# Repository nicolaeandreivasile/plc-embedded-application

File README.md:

# plc-embedded-application
A PLC (Programmable Logic Controller) made from scratch focused on controlling and maintaining industrial-like applications

## Board design
Control unit schematic under development. I/O unit schematic development process not started yet

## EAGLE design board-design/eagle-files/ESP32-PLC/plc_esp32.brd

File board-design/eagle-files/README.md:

Connected with ESP32:

	EEPROM: M95M01
	EERAM: 48L512T
	-------------- 7 pins (VSPI)
	
	RTC: MCP7940N
	-------------- 3 pins (I2C)
	
	Volt. supervisor: BD48E30G
	-------------- 1 pin (ESP enable)
	
	I/O controller
	-------------- 7 pins (HSPI)
	
	UART0
	-------------- 2 pins (RXD/TXD)
	
Unconnected with ESP32:

	LTE: EC20
	-------------- 5 pins
	
	RS-422/485: MAX3485CSA
	-------------- 4 pins
	
	+ other optional modules
	
No pins left for ESP32 module! Another approach needed.

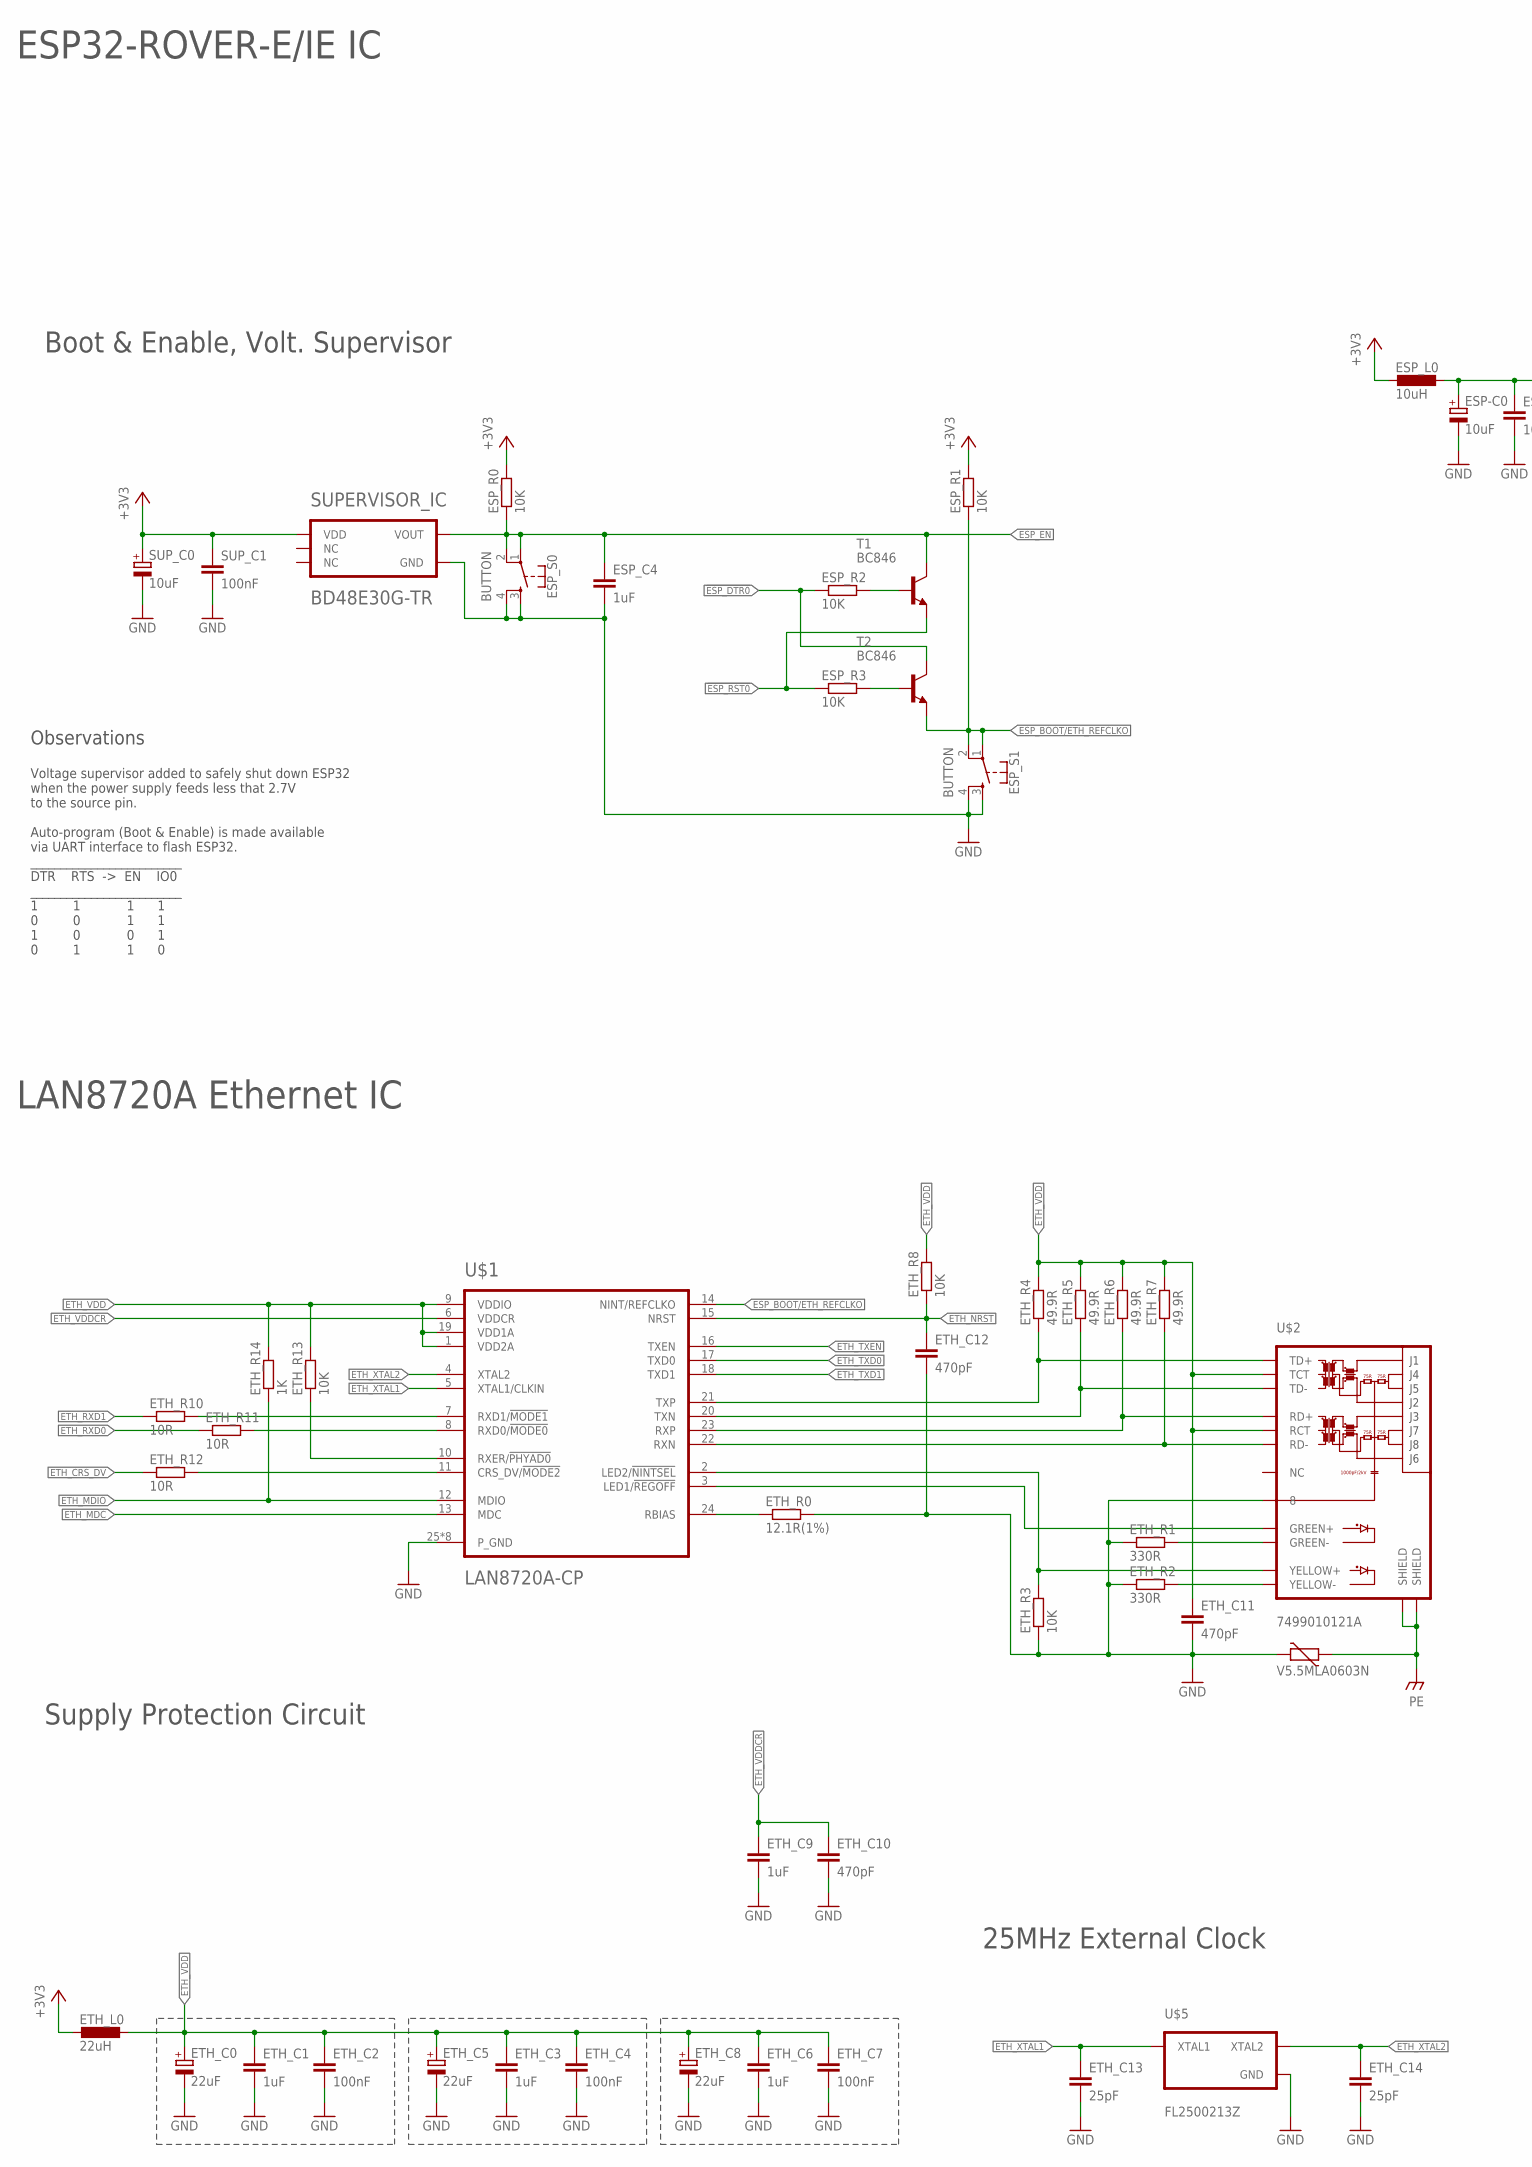
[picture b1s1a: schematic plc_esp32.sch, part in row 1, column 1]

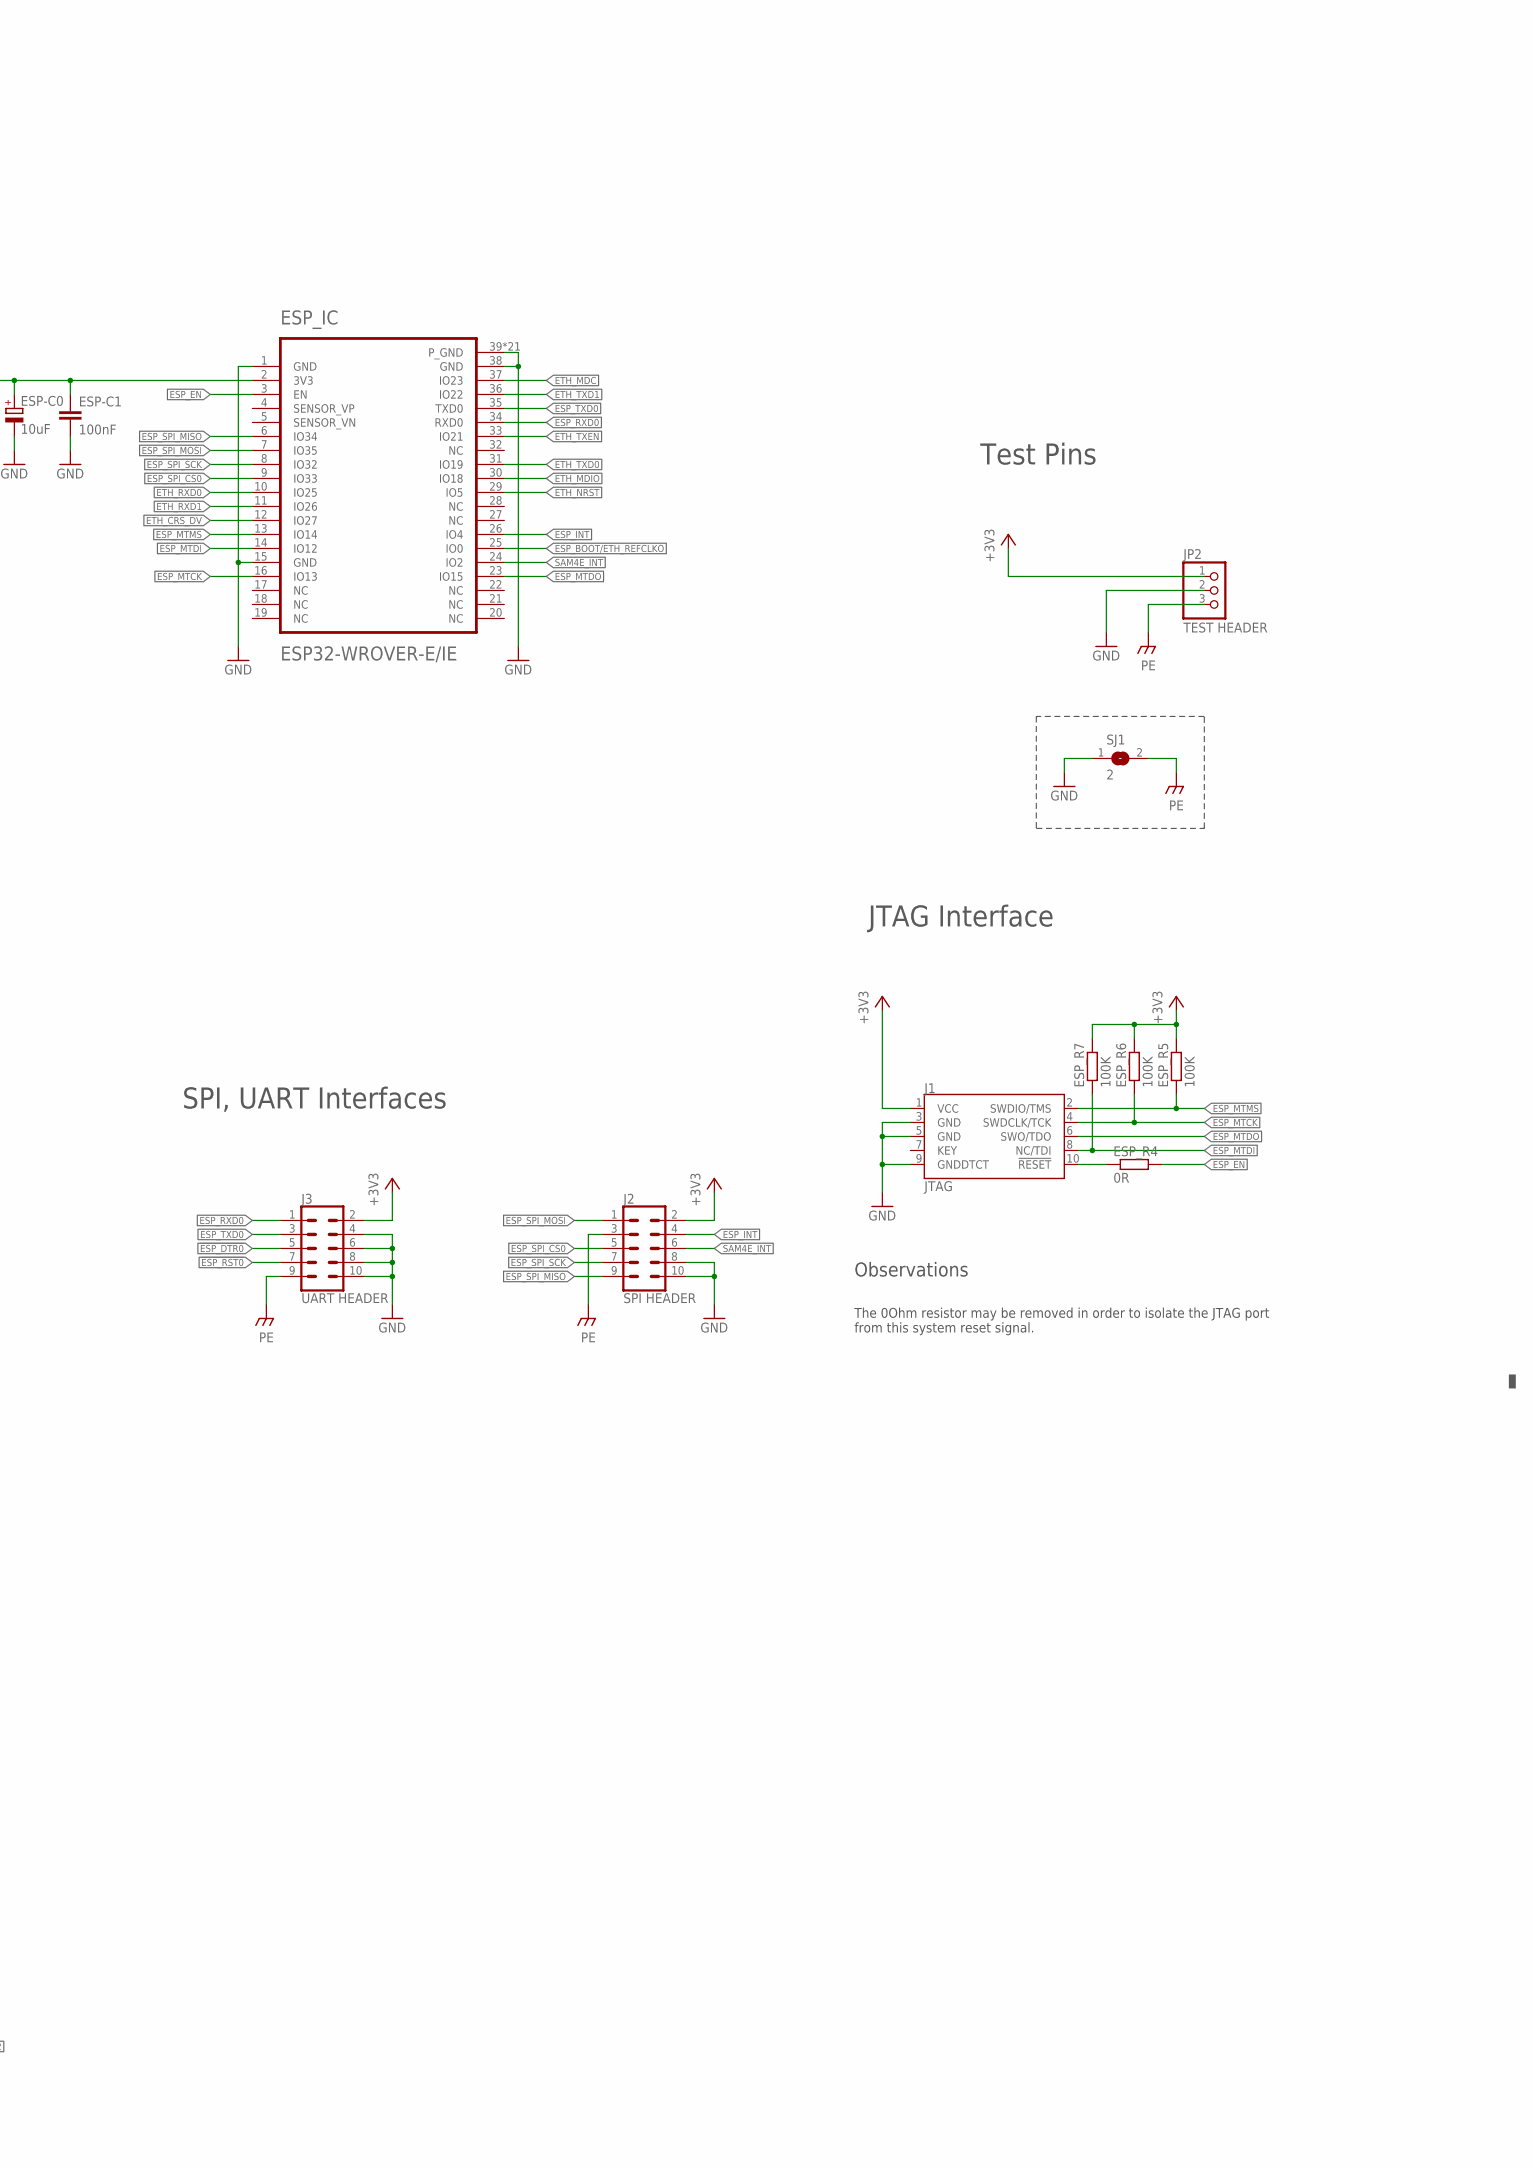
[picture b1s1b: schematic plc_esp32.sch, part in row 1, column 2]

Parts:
ESP-C0: 10uF; SMC_B
ESP-C1: 100nF; C0402
ESP_C4: 1uF; C0402
ESP_IC: ESP32-WROVER-E/IE
ESP_L0: 10uH; L1812
ESP_R0, ESP_R1, ESP_R2, ESP_R3: 10K; R0402
ESP_R4: 0R; R0402
ESP_R5, ESP_R6, ESP_R7: 100K; R0402
ESP_S0, ESP_S1: BUTTON; TACTILE_SWITCH_SMD_4.6X2.8MM
ETH_C0, ETH_C5, ETH_C8: 22uF; SMC_B
ETH_C1, ETH_C3, ETH_C6, ETH_C9: 1uF; C0402
ETH_C2, ETH_C4, ETH_C7: 100nF; C0402
ETH_C10, ETH_C11, ETH_C12: 470pF; C0402
ETH_C13, ETH_C14: 25pF; C0402
ETH_L0: 22uH; L1812
ETH_R0: 12.1R(1%); R0402
ETH_R1, ETH_R2: 330R; R0402
ETH_R3, ETH_R8, ETH_R13: 10K; R0402
ETH_R4, ETH_R5, ETH_R6, ETH_R7: 49.9R; R0402
ETH_R10, ETH_R11, ETH_R12: 10R; R0402
ETH_R14: 1K; R0402
J1: JTAG; 2X5-SMD-1.27MM
J2: SPI HEADER; 2X5-SHROUDED_SMD
J3: UART HEADER; 2X5-SHROUDED_SMD
JP2: TEST HEADER; 1X03
MCU_VAR1: V5.5MLA0603N; CT/CN0603
SJ1: 2; SJ
SUPERVISOR_IC: BD48E30G-TR; SSOP5
SUP_C0: 10uF; SMC_B
SUP_C1: 100nF; C0402
T1, T2: BC846; SOT23
U$1: LAN8720A-CP; QFN-24(4X4MM)
U$2: 7499010121A; RJ45-7499010121A
U$5: FL2500213Z; 3.2X2.5MM

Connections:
!ESP_DTR0: ESP_R2.1, J3.5, T2.3 (C)
!ESP_RST0: ESP_R3.1, J3.7, T1.2 (E)
+3V3: ESP_L0.2, ESP_R0.2, ESP_R1.2, ESP_R5.2, ESP_R6.2, ESP_R7.2, ETH_L0.2, J1.1 (VCC), J2.2, J3.2, JP2.1, SUPERVISOR_IC.2 (VDD), SUP_C0.+, SUP_C1.1
ESP_3V3: ESP-C0.+, ESP-C1.1, ESP_IC.2 (3V3), ESP_L0.1
ESP_BOOT/ETH_REFCLKO: ESP_IC.25 (IO0), ESP_R1.1, ESP_S1.1, ESP_S1.2, T2.2 (E), U$1.14 (NINT/REFCLKO)
ESP_EN: ESP_C4.1, ESP_IC.3 (EN), ESP_R0.1, ESP_R4.2, ESP_S0.1, ESP_S0.2, SUPERVISOR_IC.1 (VOUT), T1.3 (C)
ESP_INT: ESP_IC.26 (IO4), J2.4
ESP_MTCK: ESP_IC.16 (IO13), ESP_R6.1, J1.4 (SWDCLK/TCK)
ESP_MTDI: ESP_IC.14 (IO12), ESP_R7.1, J1.8 (NC/TDI)
ESP_MTDO: ESP_IC.23 (IO15), J1.6 (SWO/TDO)
ESP_MTMS: ESP_IC.13 (IO14), ESP_R5.1, J1.2 (SWDIO/TMS)
ESP_RXD0: ESP_IC.34 (RXD0), J3.1
ESP_SPI_CS0: ESP_IC.9 (IO33), J2.5
ESP_SPI_MISO: ESP_IC.6 (IO34), J2.9
ESP_SPI_MOSI: ESP_IC.7 (IO35), J2.1
ESP_SPI_SCK: ESP_IC.8 (IO32), J2.7
ESP_TXD0: ESP_IC.35 (TXD0), J3.3
ETH_CRS_DV: ESP_IC.12 (IO27), ETH_R12.1
ETH_MDC: ESP_IC.37 (IO23), U$1.13 (MDC)
ETH_MDIO: ESP_IC.30 (IO18), ETH_R14.1, U$1.12 (MDIO)
ETH_NRST: ESP_IC.29 (IO5), ETH_C12.1, ETH_R8.1, U$1.15 (NRST)
ETH_RJ45_LED2: ETH_R3.2, U$1.2 (LED2/!NINTSEL), U$2.12 (YELLOW+)
ETH_RJ45_RXN: ETH_R7.1, U$1.22 (RXN), U$2.6 (RD-)
ETH_RJ45_RXP: ETH_R6.1, U$1.23 (RXP), U$2.4 (RD+)
ETH_RJ45_TXN: ETH_R5.1, U$1.20 (TXN), U$2.3 (TD-)
ETH_RJ45_TXP: ETH_R4.1, U$1.21 (TXP), U$2.1 (TD+)
ETH_RXD0: ESP_IC.10 (IO25), ETH_R11.1
ETH_RXD1: ESP_IC.11 (IO26), ETH_R10.1
ETH_TXD0: ESP_IC.31 (IO19), U$1.17 (TXD0)
ETH_TXD1: ESP_IC.36 (IO22), U$1.18 (TXD1)
ETH_TXEN: ESP_IC.33 (IO21), U$1.16 (TXEN)
ETH_VDD: ETH_C0.+, ETH_C1.1, ETH_C2.1, ETH_C3.1, ETH_C4.1, ETH_C5.+, ETH_C6.1, ETH_C7.1, ETH_C8.+, ETH_C11.1, ETH_L0.1, ETH_R4.2, ETH_R5.2, ETH_R6.2, ETH_R7.2, ETH_R8.2, ETH_R13.2, ETH_R14.2, U$1.1 (VDD2A), U$1.9 (VDDIO), U$1.19 (VDD1A), U$2.2 (TCT), U$2.5 (RCT)
ETH_VDDCR: ETH_C9.1, ETH_C10.1, U$1.6 (VDDCR)
ETH_XTAL1: ETH_C13.1, U$1.5 (XTAL1/CLKIN), U$5.1 (XTAL1)
ETH_XTAL2: ETH_C14.1, U$1.4 (XTAL2), U$5.3 (XTAL2)
GND: ESP-C0.-, ESP-C1.2, ESP_C4.2, ESP_IC.1 (GND), ESP_IC.15 (GND), ESP_IC.38 (GND), ESP_IC.39 (P_GND), ESP_IC.40 (P_GND), ESP_IC.41 (P_GND), ESP_IC.42 (P_GND), ESP_IC.43 (P_GND), ESP_IC.44 (P_GND), ESP_IC.45 (P_GND), ESP_IC.46 (P_GND), ESP_IC.47 (P_GND), ESP_IC.48 (P_GND), ESP_IC.49 (P_GND), ESP_IC.50 (P_GND), ESP_IC.51 (P_GND), ESP_IC.52 (P_GND), ESP_IC.53 (P_GND), ESP_IC.54 (P_GND), ESP_IC.55 (P_GND), ESP_IC.56 (P_GND), ESP_IC.57 (P_GND), ESP_IC.58 (P_GND), ESP_IC.59 (P_GND), ESP_S0.3, ESP_S0.4, ESP_S1.3, ESP_S1.4, ETH_C0.-, ETH_C1.2, ETH_C2.2, ETH_C3.2, ETH_C4.2, ETH_C5.-, ETH_C6.2, ETH_C7.2, ETH_C8.-, ETH_C9.2, ETH_C10.2, ETH_C11.2, ETH_C12.2, ETH_C13.2, ETH_C14.2, ETH_R0.2, ETH_R1.1, ETH_R2.1, ETH_R3.1, J1.3 (GND), J1.5 (GND), J1.9 (GNDDTCT), J2.8, J2.10, J3.4, J3.6, J3.8, J3.10, JP2.2, MCU_VAR1.2, SJ1.1, SUPERVISOR_IC.3 (GND), SUP_C0.-, SUP_C1.2, U$1.25 (P_GND), U$1.26 (P_GND), U$1.27 (P_GND), U$1.28 (P_GND), U$1.29 (P_GND), U$1.30 (P_GND), U$1.31 (P_GND), U$1.32 (P_GND), U$2.8, U$5.2 (GND), U$5.4 (GND)
unnamed: ETH_R0.1, U$1.24 (RBIAS)
unnamed: ETH_R10.2, U$1.7 (RXD1/!MODE1)
unnamed: ETH_R11.2, U$1.8 (RXD0/!MODE0)
unnamed: ETH_R13.1, U$1.10 (RXER/!PHYAD0)
unnamed: ESP_R4.1, J1.10 (!RESET)
unnamed: U$1.3 (LED1/!REGOFF), U$2.10 (GREEN+)
unnamed: ESP_R3.2, T2.1 (B)
unnamed: ESP_R2.2, T1.1 (B)
unnamed: ETH_R12.2, U$1.11 (CRS_DV/!MODE2)
unnamed: ETH_R1.2, U$2.9 (GREEN-)
unnamed: ETH_R2.2, U$2.11 (YELLOW-)
P$1: J2.3, J3.9, JP2.3, MCU_VAR1.1, SJ1.2, U$2.13 (SHIELD), U$2.14 (SHIELD)
SAM4E_INT: ESP_IC.24 (IO2), J2.6

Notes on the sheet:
Supply Protection Circuit
25MHz External Clock
LAN8720A Ethernet IC
Observations
The 0Ohm resistor may be removed in order to isolate the JTAG port from this system reset signal.
JTAG Interface
Boot & Enable, Volt. Supervisor
Voltage supervisor added to safely shut down ESP32 when the power supply feeds less that 2.7V to the source pin. Auto-program (Boot & Enable) is made available via UART interface to flash ESP32. _________________________ DTR RTS -> EN IO0 _________________________ 1 1 1 1 0 0 1 1 1 0 0 1 0 1 1 0
SPI, UART Interfaces
Test Pins
ESP32-ROVER-E/IE IC

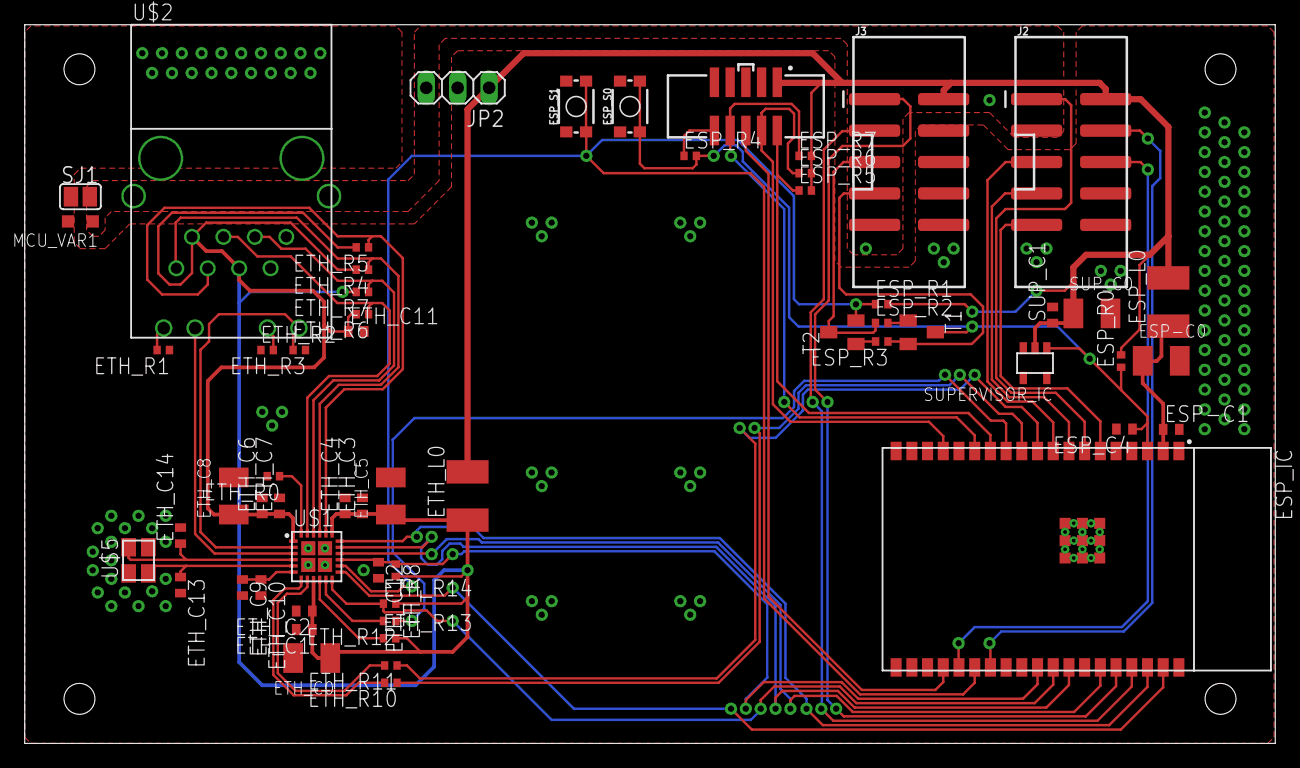
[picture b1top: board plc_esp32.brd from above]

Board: 2 copper layers, 101.1 x 58.1 mm, 59 parts (0 on the bottom side), 49 nets.

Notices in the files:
parts and their libraries:
SparkFun-Connectors: Licensing: Creative Commons ShareAlike 4.0 International - https://creativecommons.org/licenses/by-sa/4.0
